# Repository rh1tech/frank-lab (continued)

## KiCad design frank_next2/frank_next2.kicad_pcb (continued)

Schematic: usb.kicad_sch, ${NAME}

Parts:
C1: 330 µF 6.3 V; CP_Elec_6.3x6.0
C3, C12, C14, C16, C17, C21, C22, C31, C73, C77, C86: 10 µF 25 V; C_0603_1608Metric_small_pads_Via_GND; LCSC C96446
C10, C19, C20, C69: 100 nF 50 V; C_0603_1608Metric_small_pads_Via_GND; LCSC C14663
C15: 100 µF 16 V; CP_Elec_6.3x6.0; LCSC C19270701
C26, C29: 12 pF 50 V; C_0603_1608Metric; LCSC C107034; not fitted
C30: 1 µF 50 V; C_0603_1608Metric_small_pads_Via_GND; LCSC C5199872
C76: 47 nF 50 V; C_0603_1608Metric_small_pads_Via; LCSC C1622
C85: 22 pF 50 V; C_0603_1608Metric_small_pads_Via; LCSC C1653
D1, D2: SMAJ5.0A; D_SMA; LCSC C83329
F2, F3: 2.6 A 6 V; Fuse_1812_4532Metric
J13, J14: USB4215-03-A; USB_C_Receptacle; LCSC C37616412
JP1: PWR Debug; SolderJumper-2_P1.3mm_Open_RoundedPad1.0x1.5mm
L3: 2.2 µH; L_Cenker_CKCS3015; LCSC C167747
L4: 330 Ω@100 MHz 2.5 A; L_0805_2012Metric; LCSC C76819
LD3: Green; LED_0603_1608Metric; LCSC C965804
R18, R47, R49, R52: 5.1 kΩ; R_0603_1608Metric; LCSC C23186
R19: 4.7 kΩ; R_0603_1608Metric; LCSC C23162; not fitted
R21: 39 kΩ; R_0603_1608Metric; LCSC C23153
R37: 300 kΩ; R_0603_1608Metric_small_pads_Via; LCSC C23024
R38: 1 MΩ; R_0603_1608Metric; LCSC C22935; not fitted
R39: 1 MΩ; R_0603_1608Metric_small_pads_Via; LCSC C22935
R42: 22 kΩ 1%; R_0603_1608Metric; LCSC C31850
R43: 100 kΩ 1%; R_0603_1608Metric_small_pads_Via; LCSC C25803
R45: 100 kΩ; R_0603_1608Metric; LCSC C25803
R53: 1 kΩ; R_0603_1608Metric_small_pads_Via; LCSC C21190
R57: 22 kΩ; R_0603_1608Metric; LCSC C31850
S5: SK12D07VG3NS; Switch_Slide_SK12D07VG3NS_PWR; Mouser Part Number 611-SK12D07VG3NS; LCSC C431547
TP2: VDD33; TestPoint_Pad_D1.0mm
TP5: VBUS; TestPoint_Pad_D1.0mm
TP6: VBUS_IN1; TestPoint_Pad_D1.0mm
TP7: VBUS_IN; TestPoint_Pad_D1.0mm
TP8: +5V_BUCK; TestPoint_Pad_D1.0mm
TP11: VBUS_IN2; TestPoint_Pad_D1.0mm
TP12: +3V3; TestPoint_Pad_D1.0mm
U5: TS3USB221RSER; UQFN-10; LCSC C130085
U6: SY8089AAAC; SOT-23-5; LCSC C78988
U8: TPS2116DRL; SOT-583-8; LCSC C3235557
U10, U11: TPD4S012DRYR; Mouser Part Number 595-TPD4S012DRYR; LCSC C96506
U16: CH334F; QFN-24-1EP_4x4mm_P0.5mm_EP2.7x2.7mm; LCSC C5187527
U17: CH217A; SOT-23-6; LCSC C54973763
U23: AO3401A; SOT-23-3L_AOS; LCSC C15127
Y1: 12 MHz; Crystal_SMD_3225-4Pin_3.2x2.5mm; LCSC C20625731

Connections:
+3V3: C10.1, C16.1, C17.1, C85.1, C86.1, L3.1, R43.1, R53.1, TP12.1 (1_1), U5.10 (VCC); also elsewhere on the board
/RP2350B/M_USB_DM: U5.7 (D-); also elsewhere on the board
/RP2350B/M_USB_DP: U5.8 (D+); also elsewhere on the board
/USB/+5V_BUCK: C12.1, C69.1, C77.1, L4.2, TP8.1 (1_1), U6.1 (EN), U6.4 (IN)
/USB/S_USB_DM: J13.5 (DN2), J13.7 (DN1), U10.2 (D-_); also elsewhere on the board
/USB/S_USB_DP: J13.6 (DP1), J13.8 (DP2), U10.1 (D+); also elsewhere on the board
/USB/US_D2+: J14.6 (DP1), J14.8 (DP2), U5.1 (1D+), U11.1 (D+)
/USB/US_D2-: J14.5 (DN2), J14.7 (DN1), U5.2 (1D-), U11.2 (D-_)
/USB/US_DH+: U5.3 (2D+), U16.15 (DPU+)
/USB/US_DH-: U5.4 (2D-), U16.14 (DMU-)
/USB/US_DS1+: U16.12 (DP1+); also elsewhere on the board
/USB/US_DS1-: U16.11 (DM1-); also elsewhere on the board
/USB/US_DS2+: U16.10 (DP2+); also elsewhere on the board
/USB/US_DS2-: U16.9 (DM2-); also elsewhere on the board
/USB/US_DS3+: U16.8 (DP3+); also elsewhere on the board
/USB/US_DS3-: U16.7 (DM3-); also elsewhere on the board
/USB/US_OVCUR: U16.1 (~OVCUR), U17.3 (FLAG#)
/USB/US_PWREN: U16.24 (~PWREN), U17.4 (EN#)
/USB/US_ST: R38.2, U8.8 (ST)
/USB/US_XTAL_N: C29.1, U16.3 (XO), Y1.3
/USB/US_XTAL_P: C26.1, U16.4 (XI), Y1.1
/USB/VBUS_A: C1.1, U17.1 (VOUT); also elsewhere on the board
/USB/VBUS_IN: C14.1, R39.1, TP7.1 (1_1), U8.2 (VOUT), U8.7 (VOUT), U23.2 (S)
/USB/VBUS_IN1: C19.1, C21.1, D1.1 (K), F2.2, R37.1, TP6.1 (1_1), U8.3 (VIN1), U8.5 (MODE)
/USB/VBUS_IN2: C20.1, C22.1, D2.1 (K), F3.2, TP11.1 (1_1), U8.6 (VIN2)
/USB/VBUS_J10: F3.1, J14.2 (VBUS), J14.11 (VBUS), U11.6 (VBUS)
/USB/VBUS_J11: F2.1, J13.2 (VBUS), J13.11 (VBUS), U10.6 (VBUS)
/USB/VDD33: C30.1, C31.1, TP2.1 (1_1), U16.20 (VDD33_{LDO})
/US_SEL: U5.9 (S); also elsewhere on the board
GND: C1.2, C3.2, C10.2, C12.2, C14.2, C15.2, C16.2, C17.2, C19.2, C20.2, C21.2, C22.2, C26.2, C29.2, C30.2, C31.2, C69.2, C73.2, C77.2, C86.2, D1.2 (A), D2.2 (A), J13.1 (GND), J13.12 (GND), J13.13 (SHIELD), J14.1 (GND), J14.12 (GND), J14.13 (SHIELD), JP1.1 (A), LD3.1 (K), R18.1, R19.2, R21.2, R42.2, R45.1, R47.1, R49.1, R52.1, S5.2, U5.5 (GND), U5.6 (~OE), U6.2 (GND), U8.1 (GND), U10.4 (GND), U11.4 (GND), U16.25 (GND), U17.2 (GND), Y1.2, Y1.4; also elsewhere on the board
unnamed: J13.4 (CC1), R49.2
unnamed: J13.10 (CC2), R18.2
unnamed: J14.4 (CC1), R47.2
unnamed: J14.10 (CC2), R52.2
unnamed: JP1.2 (B), R57.2, S5.3
unnamed: LD3.2 (A), R53.2
unnamed: C85.2, R42.1, R43.2, U6.5 (FB)
unnamed: L3.2, U6.3 (LX)
unnamed: R37.2, R38.1, R45.2, U8.4 (PR1)
unnamed: R19.1, U16.18 (PSELF)
unnamed: R21.1, U17.5 (ISET)
unnamed: C76.2, R39.2, R57.1, U23.1 (G)
VBUS: C3.1, C15.1, C73.1, C76.1, L4.1, TP5.1 (1_1), U16.19 (V5), U17.6 (VIN), U23.3 (D); also elsewhere on the board

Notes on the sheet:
F2 / F3: 2.6 A polyfuse, D1 / D2: SMAJ5.0A TVS per USB-C input (TPS2116 / CH217A / SY8089 are 6 V abs-max). U11 / U10 ESD at the connector.
Power path: J13 (VIN1) / J14 (VIN2) -> U8 TPS2116. J13 is preferred while its VBUS is above ~4 V (R37 / R45 on PR1, MODE tied to VIN1). R38: DNP. S5 -> U23 AO3401A P-FET: R39 holds it off, S5 pulls the gate low via R57, C76 = soft start. JP1 bypasses S5. VBUS -> L4 ferrite -> U6 SY8089 buck: 3V3 = 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
USB data: J13 -> RP2350A USB (direct). U5: RP2350B -> J14 (S = L, PC / BOOTSEL) or hub (S = H); S = USB_SEL from the latch. C29 / C26 DNP (CH334 has 16 pF inside). Needs a 5 V / 3 A supply.
5.1 kΩ CC pull-downs (Rd): both USB-C ports are sinks
USB-A VBUS: U17 CH217A gangs all 3 ports (CH334F gang mode), R21 39 kΩ = 1.54 A typ total. C1 330 µF polymer (Wurth 875105144010) on VBUS_A. C15 100 µF + C73 / C3 10 µF on VBUS.

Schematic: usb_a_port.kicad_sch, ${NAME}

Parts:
C25: 100 nF 50 V; C_0603_1608Metric; LCSC C14663
J3: AF 10.0 HC6.3; USB_A_Short; LCSC C456017
U15: TPD4S012DRYR; Mouser Part Number 595-TPD4S012DRYR; LCSC C96506

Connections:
/USB/US_DS1+: J3.3 (D+), U15.1 (D+); also elsewhere on the board
/USB/US_DS1-: J3.2 (D-), U15.2 (D-_); also elsewhere on the board
/USB/VBUS_A: C25.1, J3.1 (VBUS), U15.6 (VBUS); also elsewhere on the board
GND: C25.2, J3.4 (GND), J3.5 (Shield), U15.4 (GND); also elsewhere on the board

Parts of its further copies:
C23, C24: 100 nF 50 V; C_0603_1608Metric; LCSC C14663
J1, J2: AF 10.0 HC6.3; USB_A_Short; LCSC C456017
U13, U14: TPD4S012DRYR; Mouser Part Number 595-TPD4S012DRYR; LCSC C96506

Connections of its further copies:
/USB/US_DS2+: J2.3 (D+), U14.1 (D+); also elsewhere on the board
/USB/US_DS2-: J2.2 (D-), U14.2 (D-_); also elsewhere on the board
/USB/US_DS3+: J1.3 (D+), U13.1 (D+); also elsewhere on the board
/USB/US_DS3-: J1.2 (D-), U13.2 (D-_); also elsewhere on the board
/USB/VBUS_A: C23.1, C24.1, J1.1 (VBUS), J2.1 (VBUS), U13.6 (VBUS), U14.6 (VBUS); also elsewhere on the board
GND: C23.2, C24.2, J1.4 (GND), J1.5 (Shield), J2.4 (GND), J2.5 (Shield), U13.4 (GND), U14.4 (GND); also elsewhere on the board

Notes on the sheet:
VBUS_A: switched USB-A VBUS from the shared CH217A (USB sheet). C25 / C23 / C24 100 nF at the connector; TPD4S012: ESD for D+ / D- / VBUS.

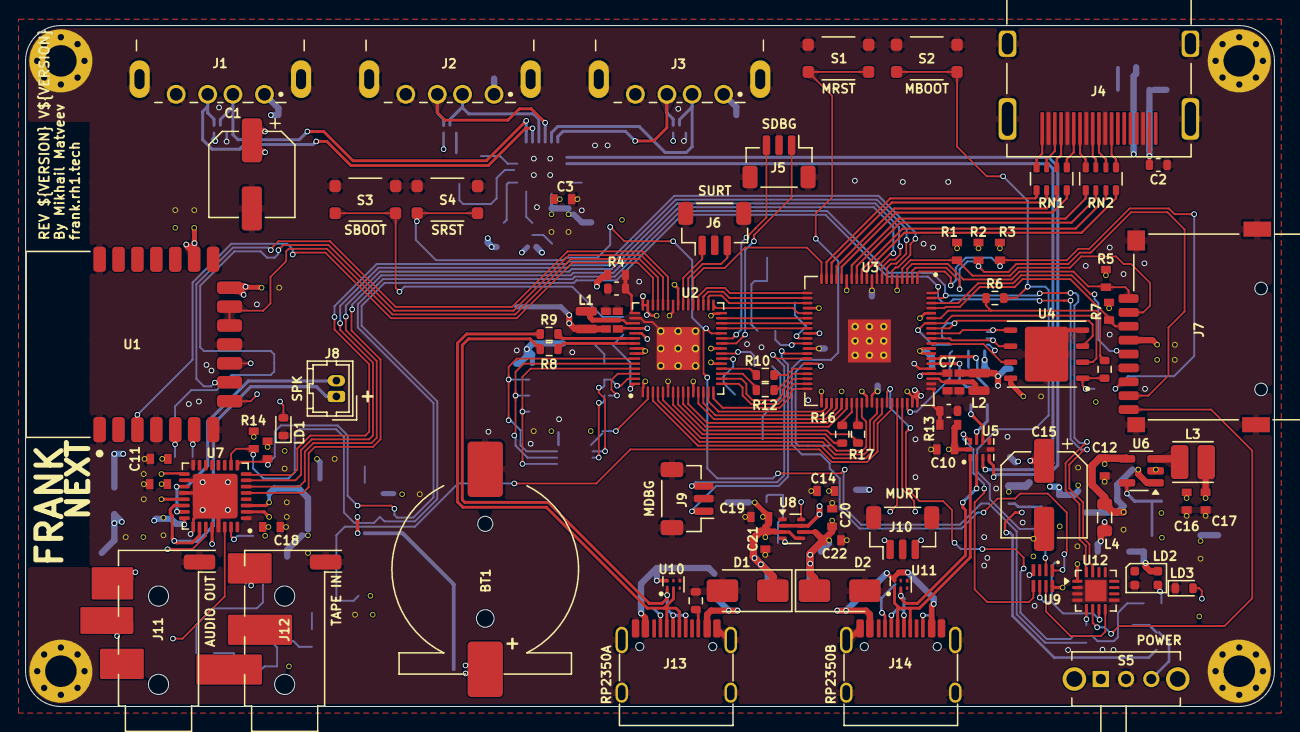
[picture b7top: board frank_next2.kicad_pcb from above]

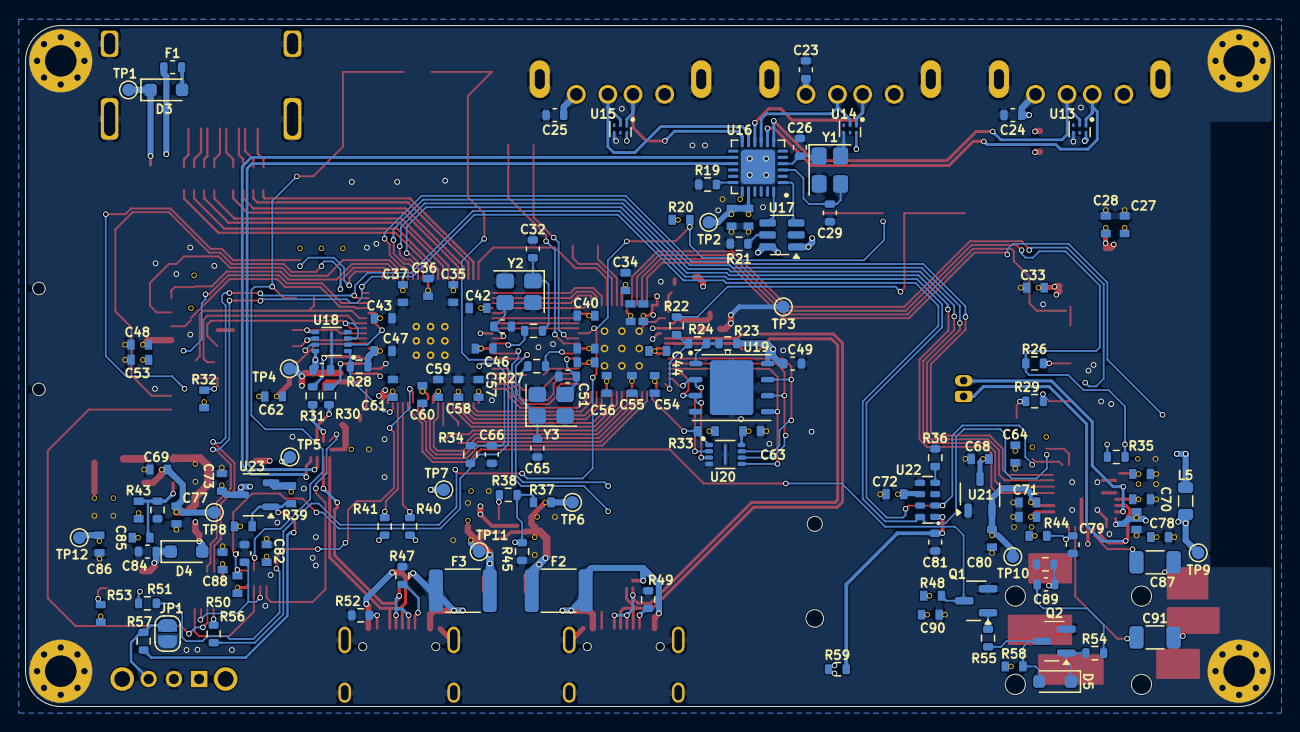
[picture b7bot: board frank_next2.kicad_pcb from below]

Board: 4 copper layers, 99.0 x 54.0 mm, 233 parts (146 on the bottom side), 180 nets.

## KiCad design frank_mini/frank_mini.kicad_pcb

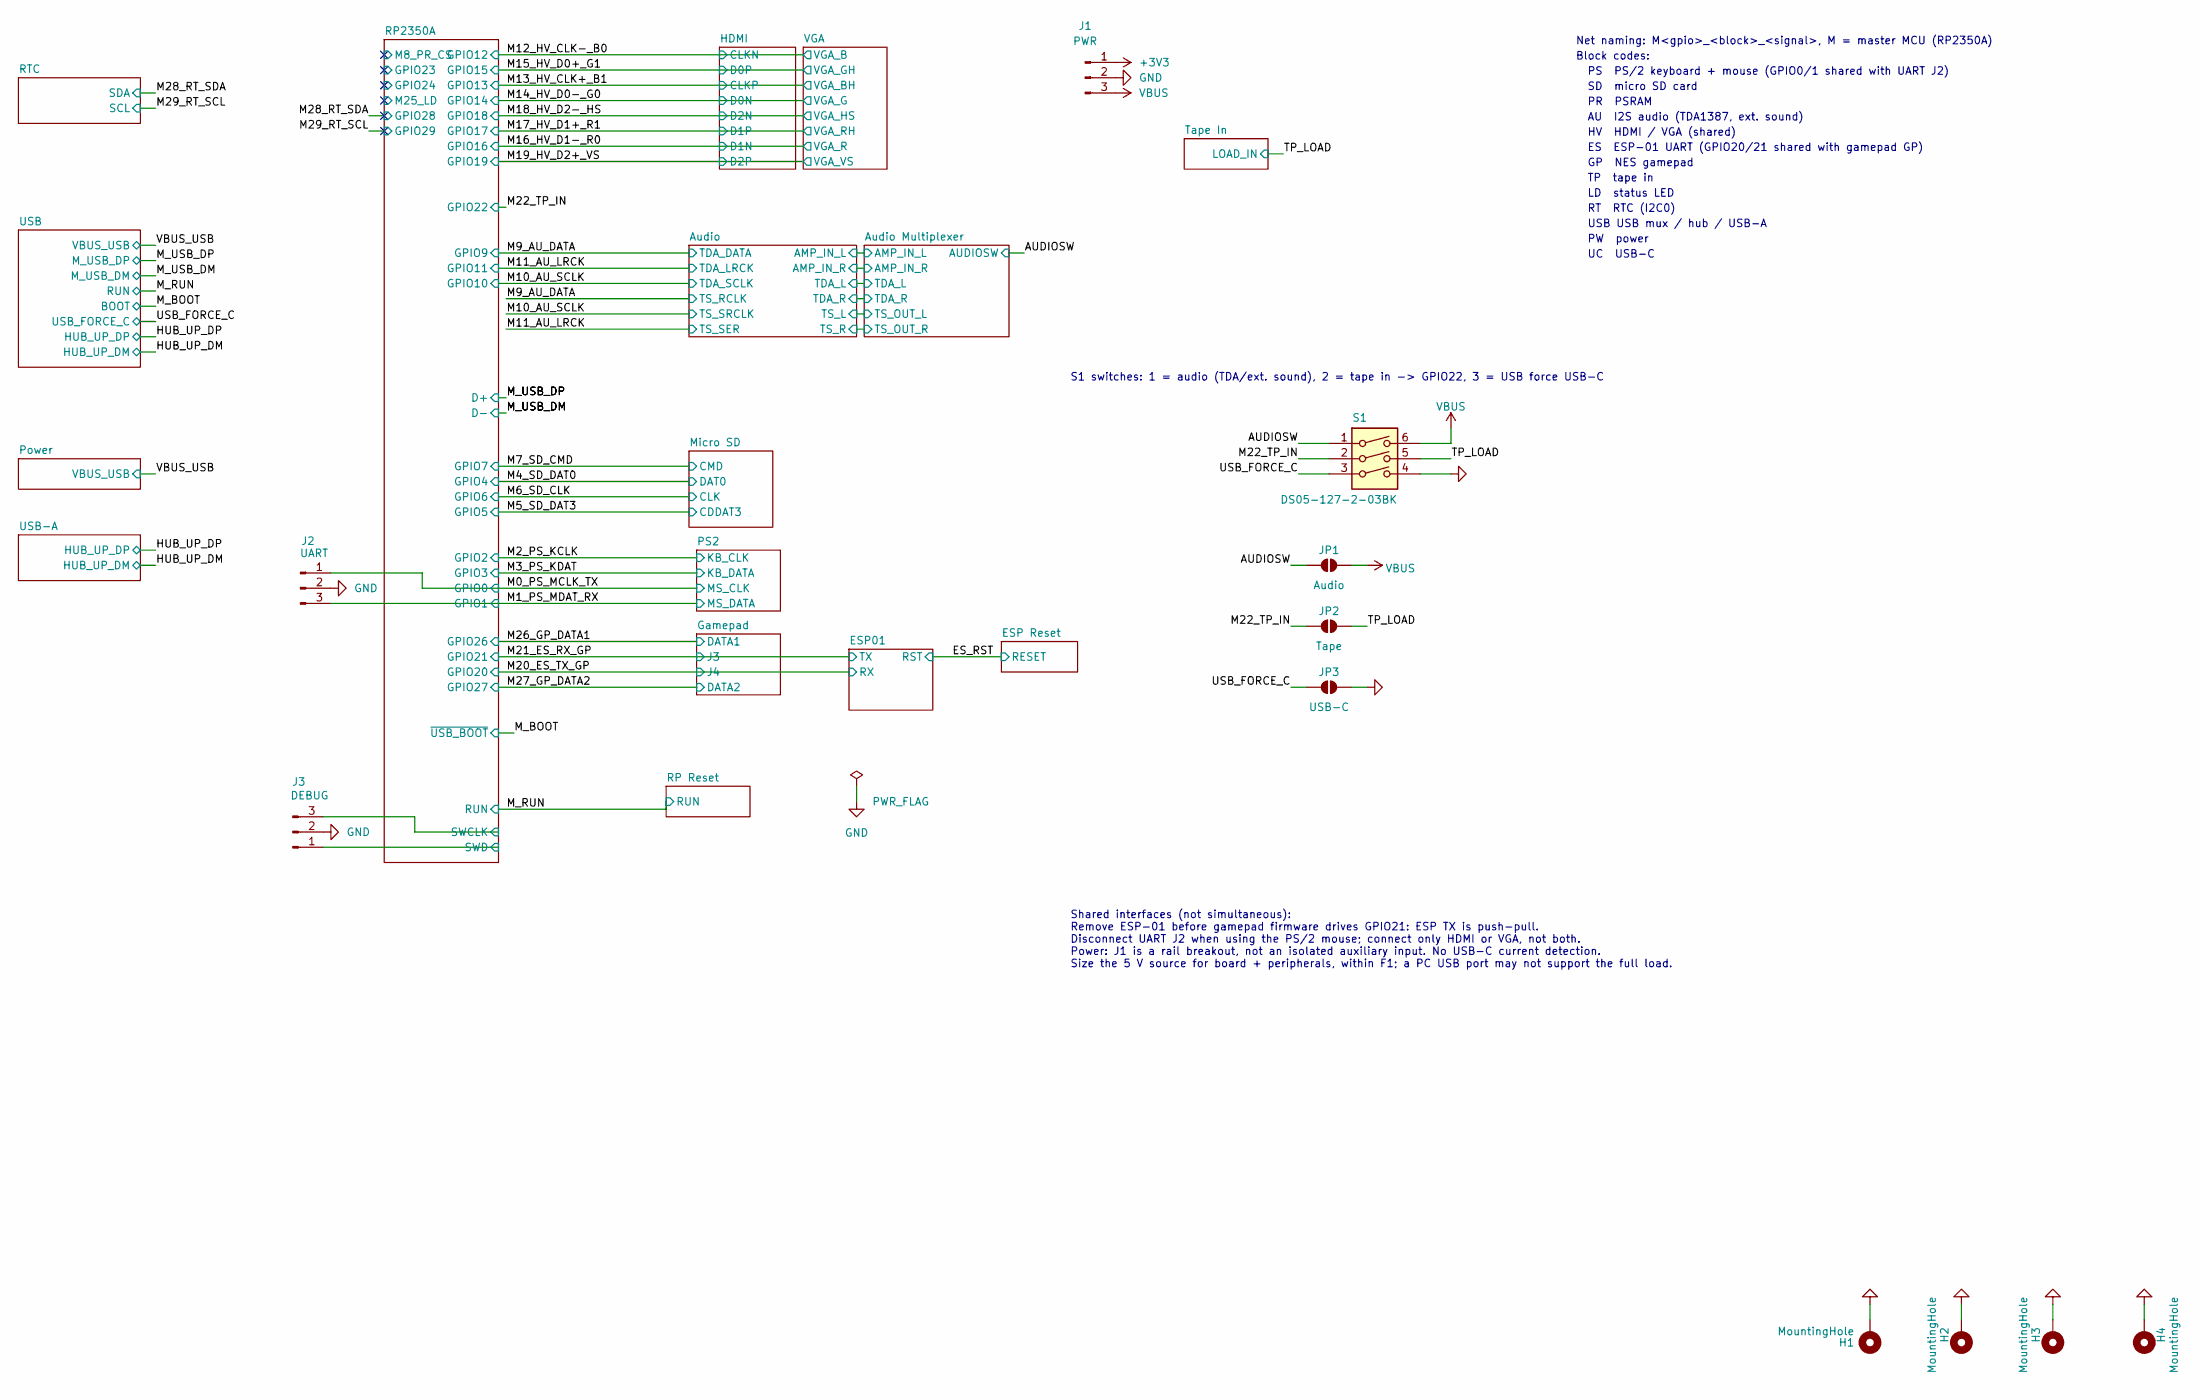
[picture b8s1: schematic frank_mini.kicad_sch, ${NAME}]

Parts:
H1, H2, H3, H4: MountingHole; MountingHole_2.5mm_Pad_Via
J1: PWR; PinHeader_1x03_P2.54mm
J2: UART; JST_SH_BM03B-SRSS-TB_1x03-1MP_P1.00mm_Vertical
J3: DEBUG; JST_SH_BM03B-SRSS-TB_1x03-1MP_P1.00mm_Vertical
JP1: Audio; SolderJumper-2_P1.3mm_Open_RoundedPad1.0x1.5mm
JP2: Tape; SolderJumper-2_P1.3mm_Open_RoundedPad1.0x1.5mm
JP3: USB-C; SolderJumper-2_P1.3mm_Open_RoundedPad1.0x1.5mm
S1: DS05-127-2-03BK; SW_DS05-127-2-03BK-SMT-TR

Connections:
+3V3: J1.1; also elsewhere on the board
/AUDIOSW: JP1.1 (A), S1.1; also elsewhere on the board
/M0_PS_MCLK_TX: J2.1; also elsewhere on the board
/M1_PS_MDAT_RX: J2.3; also elsewhere on the board
/M22_TP_IN: JP2.1 (A), S1.2; also elsewhere on the board
/RP2350A/SWCLK: J3.3; also elsewhere on the board
/RP2350A/SWD: J3.1; also elsewhere on the board
/TP_LOAD: JP2.2 (B), S1.5; also elsewhere on the board
/USB_FORCE_C: JP3.1 (A), S1.3; also elsewhere on the board
GND: H1.1 (1_1), H2.1 (1_1), H3.1 (1_1), H4.1 (1_1), J1.2, J2.2, J3.2, JP3.2 (B), S1.4; also elsewhere on the board
VBUS: J1.3, JP1.2 (B), S1.6; also elsewhere on the board

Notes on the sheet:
UC USB-C
AU I2S audio (TDA1387, ext. sound)
S1 switches: 1 = audio (TDA/ext. sound), 2 = tape in -> GPIO22, 3 = USB force USB-C
TP tape in
PS PS/2 keyboard + mouse (GPIO0/1 shared with UART J2)
SD micro SD card
USB USB mux / hub / USB-A
PW power
GP NES gamepad
RT RTC (I2C0)
Block codes:
LD status LED
PR PSRAM
Net naming: M<gpio>_<block>_<signal>, M = master MCU (RP2350A)
HV HDMI / VGA (shared)
ES ESP-01 UART (GPIO20/21 shared with gamepad GP)
Shared interfaces (not simultaneous): Remove ESP-01 before gamepad firmware drives GPIO21: ESP TX is push-pull. Disconnect UART J2 when using the PS/2 mouse; connect only HDMI or VGA, not both. Power: J1 is a rail breakout, not an isolated auxiliary input. No USB-C current detection. Size the 5 V s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

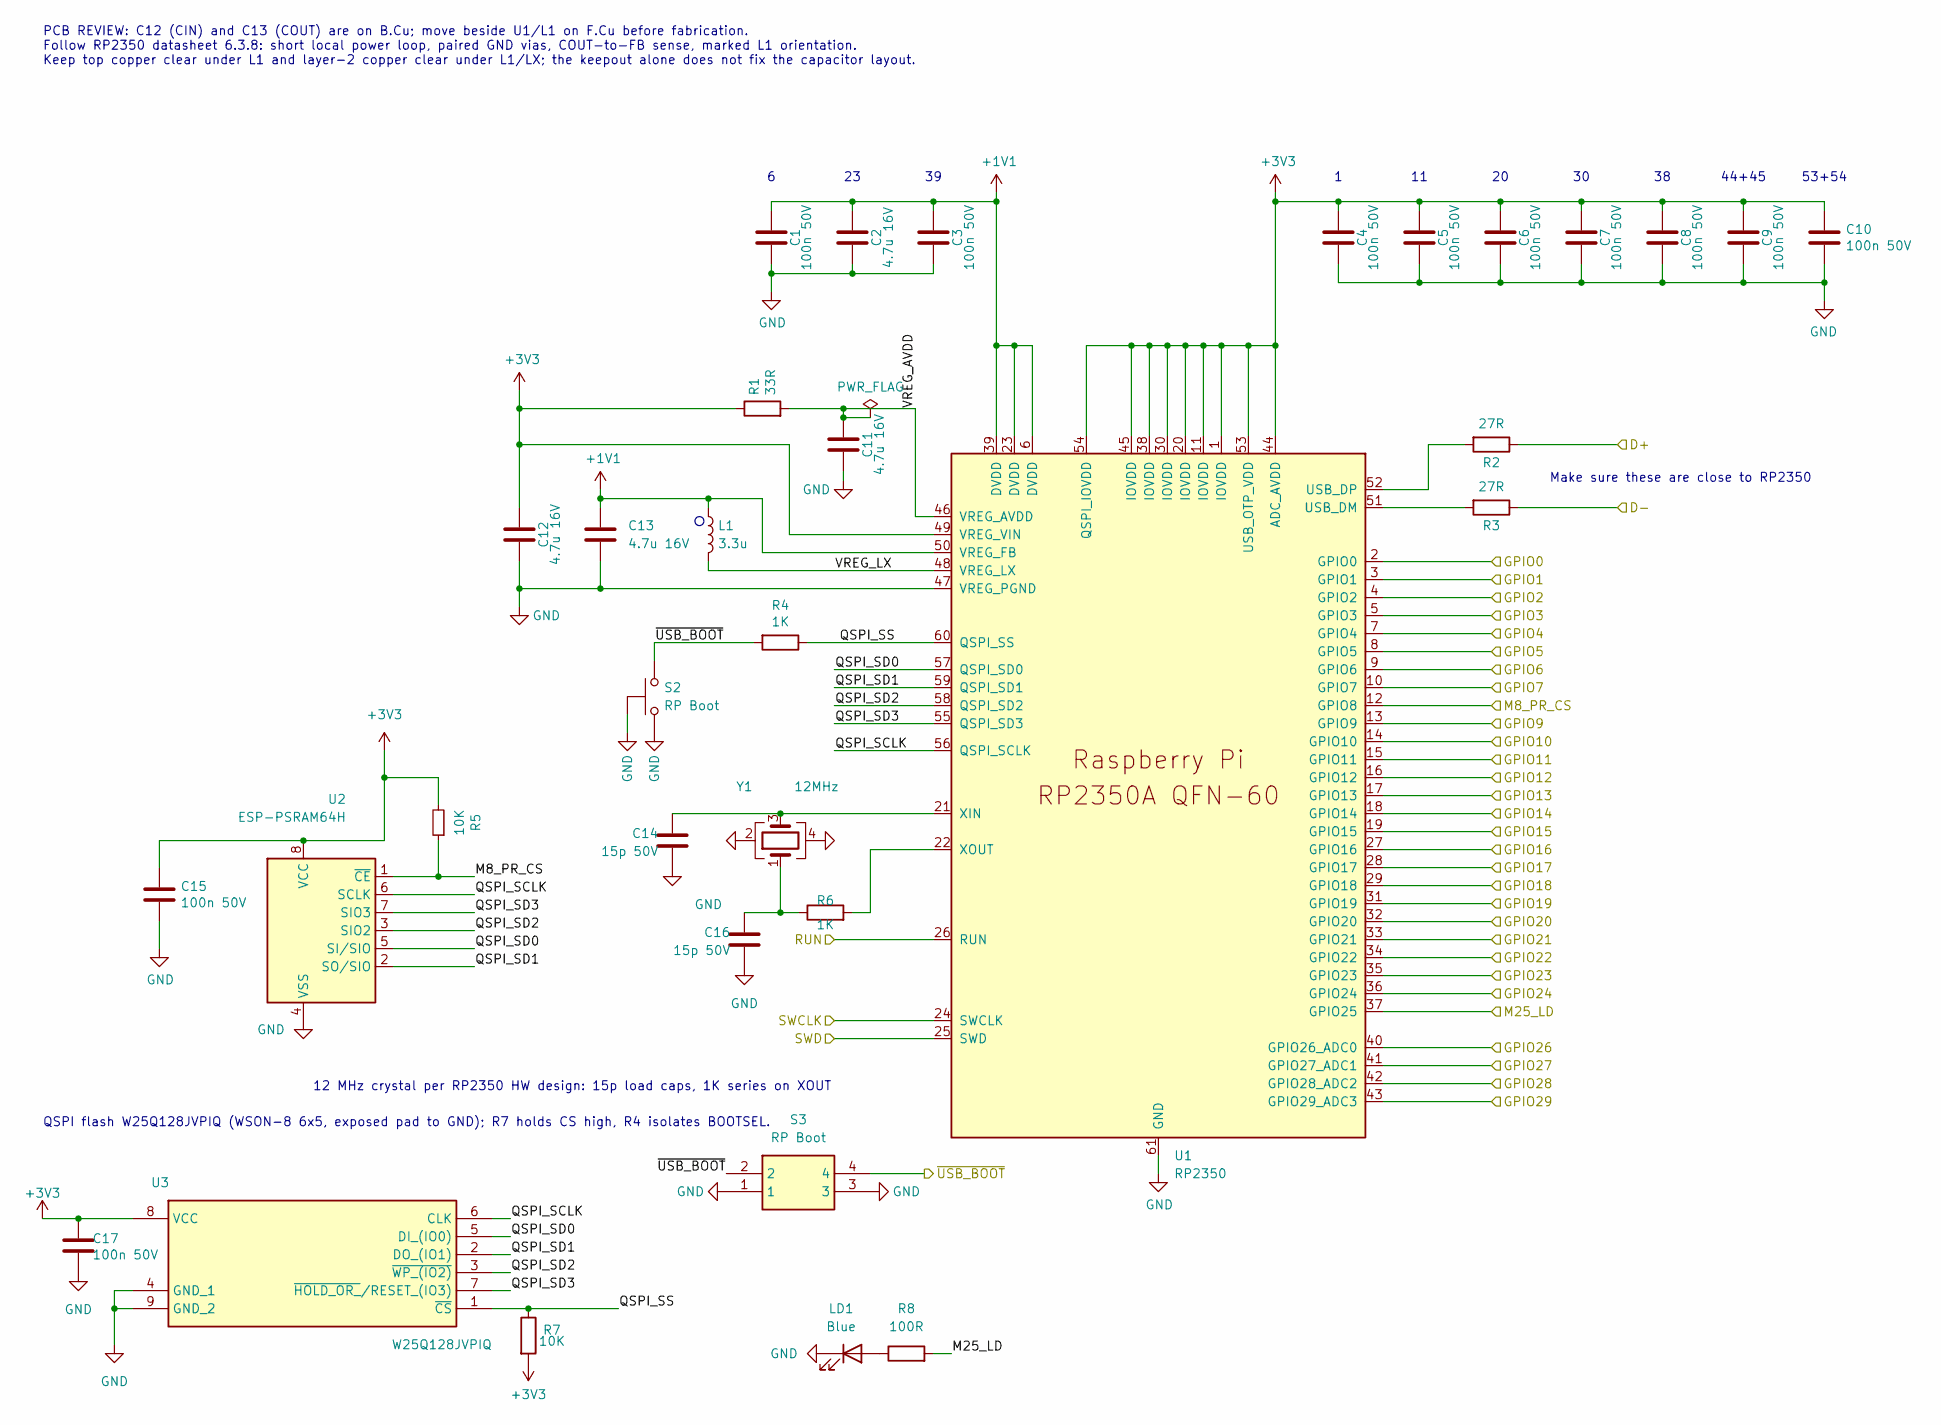
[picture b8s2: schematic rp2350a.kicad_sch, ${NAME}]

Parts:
C1, C3, C4, C5, C6, C7, C8, C9, C10, C15, C17: 100n 50V; C_0603_1608Metric
C2, C11, C12, C13: 4.7u 16V; C_0603_1608Metric
C14, C16: 15p 50V; C_0603_1608Metric
L1: 3.3u; L_pol_2016
LD1: Blue; LED_0603_1608Metric
R1: 33R; R_0603_1608Metric
R2, R3: 27R; R_0603_1608Metric
R4, R6: 1K; R_0603_1608Metric
R5, R7: 10K; R_0603_1608Metric
R8: 100R; R_0603_1608Metric
S2: RP Boot; TS-1234VW
S3: RP Boot; KMR_2; Mouser Part Number 611-KMR221G-LFS
U1: RP2350; QFN-60_RP2350A
U2: ESP-PSRAM64H; SO-8
U3: W25Q128JVPIQ; WSON-8-1EP_6x5mm_P1.27mm_EP3.45x4.35mm
Y1: 12MHz; Crystal_SMD_3225-4Pin_3.2x2.5mm

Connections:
+1V1: C1.1, C2.1, C3.1, C13.1, L1.1, U1.6 (DVDD), U1.23 (DVDD), U1.39 (DVDD), U1.50 (VREG_FB); also elsewhere on the board
+3V3: C4.1, C5.1, C6.1, C7.1, C8.1, C9.1, C10.1, C12.1, C15.1, C17.1, R1.1, R5.2, R7.2, U1.1 (IOVDD), U1.11 (IOVDD), U1.20 (IOVDD), U1.30 (IOVDD), U1.38 (IOVDD), U1.44 (ADC_AVDD), U1.45 (IOVDD), U1.49 (VREG_VIN), U1.53 (USB_OTP_VDD), U1.54 (QSPI_IOVDD), U2.8 (VCC), U3.8 (VCC); also elsewhere on the board
/M0_PS_MCLK_TX: U1.2 (GPIO0); also elsewhere on the board
/M1_PS_MDAT_RX: U1.3 (GPIO1); also elsewhere on the board
/M2_PS_KCLK: U1.4 (GPIO2); also elsewhere on the board
/M3_PS_KDAT: U1.5 (GPIO3); also elsewhere on the board
/M4_SD_DAT0: U1.7 (GPIO4); also elsewhere on the board
/M5_SD_DAT3: U1.8 (GPIO5); also elsewhere on the board
/M6_SD_CLK: U1.9 (GPIO6); also elsewhere on the board
/M7_SD_CMD: U1.10 (GPIO7); also elsewhere on the board
/M9_AU_DATA: U1.13 (GPIO9); also elsewhere on the board
/M10_AU_SCLK: U1.14 (GPIO10); also elsewhere on the board
/M11_AU_LRCK: U1.15 (GPIO11); also elsewhere on the board
/M12_HV_CLK-_B0: U1.16 (GPIO12); also elsewhere on the board
/M13_HV_CLK+_B1: U1.17 (GPIO13); also elsewhere on the board
/M14_HV_D0-_G0: U1.18 (GPIO14); also elsewhere on the board
/M15_HV_D0+_G1: U1.19 (GPIO15); also elsewhere on the board
/M16_HV_D1-_R0: U1.27 (GPIO16); also elsewhere on the board
/M17_HV_D1+_R1: U1.28 (GPIO17); also elsewhere on the board
/M18_HV_D2-_HS: U1.29 (GPIO18); also elsewhere on the board
/M19_HV_D2+_VS: U1.31 (GPIO19); also elsewhere on the board
/M20_ES_TX_GP: U1.32 (GPIO20); also elsewhere on the board
/M21_ES_RX_GP: U1.33 (GPIO21); also elsewhere on the board
/M22_TP_IN: U1.34 (GPIO22); also elsewhere on the board
/M26_GP_DATA1: U1.40 (GPIO26_ADC0); also elsewhere on the board
/M27_GP_DATA2: U1.41 (GPIO27_ADC1); also elsewhere on the board
/M28_RT_SDA: U1.42 (GPIO28_ADC2); also elsewhere on the board
/M29_RT_SCL: U1.43 (GPIO29_ADC3); also elsewhere on the board
/M_BOOT: R4.2, S2.2, S3.2, S3.4; also elsewhere on the board
/M_RUN: U1.26 (RUN); also elsewhere on the board
/M_USB_DM: R3.1; also elsewhere on the board
/M_USB_DP: R2.1; also elsewhere on the board
/RP2350A/GPIO23: U1.35 (GPIO23)
/RP2350A/GPIO24: U1.36 (GPIO24)
/RP2350A/M8_PR_CS: R5.1, U1.12 (GPIO8), U2.1 (~CE)
/RP2350A/M25_LD: R8.2, U1.37 (GPIO25)
/RP2350A/QSPI_SCLK: U1.56 (QSPI_SCLK), U2.6 (SCLK), U3.6 (CLK)
/RP2350A/QSPI_SD0: U1.57 (QSPI_SD0), U2.5 (SI/SIO), U3.5 (DI_(IO0))
/RP2350A/QSPI_SD1: U1.59 (QSPI_SD1), U2.2 (SO/SIO), U3.2 (DO_(IO1))
/RP2350A/QSPI_SD2: U1.58 (QSPI_SD2), U2.3 (SIO2), U3.3 (~WP_(IO2))
/RP2350A/QSPI_SD3: U1.55 (QSPI_SD3), U2.7 (SIO3), U3.7 (~HOLD_OR_/RESET_(IO3))
/RP2350A/QSPI_SS: R4.1, R7.1, U1.60 (QSPI_SS), U3.1 (~CS)
/RP2350A/SWCLK: U1.24 (SWCLK); also elsewhere on the board
/RP2350A/SWD: U1.25 (SWD); also elsewhere on the board
/RP2350A/VREG_AVDD: C11.1, R1.2, U1.46 (VREG_AVDD)
/RP2350A/VREG_LX: L1.2, U1.48 (VREG_LX)
GND: C1.2, C2.2, C3.2, C4.2, C5.2, C6.2, C7.2, C8.2, C9.2, C10.2, C11.2, C12.2, C13.2, C14.2, C15.2, C16.2, C17.2, LD1.1 (K), S2.1, S2.3 (GND), S3.1, S3.3, U1.47 (VREG_PGND), U1.61 (GND), U2.4 (VSS), U3.4 (GND_1), U3.9 (GND_2), Y1.2, Y1.4; also elsewhere on the board
unnamed: C16.1, R6.1, Y1.1
unnamed: LD1.2 (A), R8.1
unnamed: R3.2, U1.51 (USB_DM)
unnamed: R2.2, U1.52 (USB_DP)
unnamed: C14.1, U1.21 (XIN), Y1.3
unnamed: R6.2, U1.22 (XOUT)

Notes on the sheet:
12 MHz crystal per RP2350 HW design: 15p load caps, 1K series on XOUT
53+54
44+45
Make sure these are close to RP2350
QSPI flash W25Q128JVPIQ (WSON-8 6x5, exposed pad to GND); R7 holds CS high, R4 isolates BOOTSEL.
PCB REVIEW: C12 (CIN) and C13 (COUT) are on B.Cu; move beside U1/L1 on F.Cu before fabrication. Follow RP2350 datasheet 6.3.8: short local power loop, paired GND vias, COUT-to-FB sense, marked L1 orientation. Keep top copper clear under L1 and layer-2 copper clear under L1/LX; the keepout alone doe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

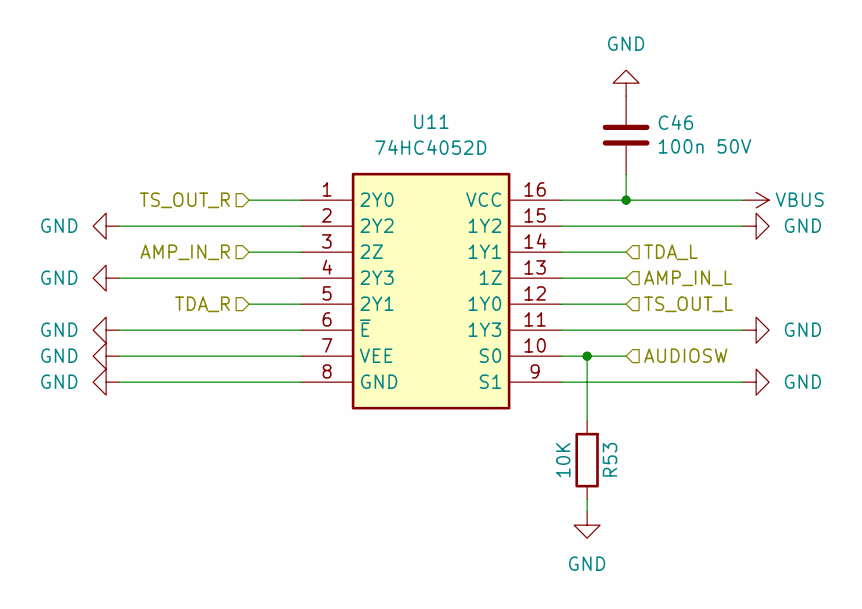
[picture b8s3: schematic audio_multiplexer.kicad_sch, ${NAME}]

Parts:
C46: 100n 50V; C_0603_1608Metric
R53: 10K; R_0603_1608Metric
U11: 74HC4052D; SOP-16_P1.27mm; Mouser Part Number 771-74HC4052D-T

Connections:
/AUDIOSW: R53.2, U11.10 (S0); also elsewhere on the board
/Audio Multiplexer/AMP_IN_L: U11.13 (1Z); also elsewhere on the board
/Audio Multiplexer/AMP_IN_R: U11.3 (2Z); also elsewhere on the board
/Audio Multiplexer/TDA_L: U11.14 (1Y1); also elsewhere on the board
/Audio Multiplexer/TDA_R: U11.5 (2Y1); also elsewhere on the board
/Audio Multiplexer/TS_OUT_L: U11.12 (1Y0); also elsewhere on the board
/Audio Multiplexer/TS_OUT_R: U11.1 (2Y0); also elsewhere on the board
GND: C46.1, R53.1, U11.2 (2Y2), U11.4 (2Y3), U11.6 (~E), U11.7 (VEE), U11.8 (GND), U11.9 (S1), U11.11 (1Y3), U11.15 (1Y2); also elsewhere on the board
VBUS: C46.2, U11.16 (VCC); also elsewhere on the board

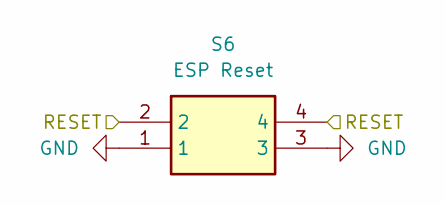
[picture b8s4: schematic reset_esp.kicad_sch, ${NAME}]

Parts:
S6: ESP Reset; KMR_2; Mouser Part Number 611-KMR221G-LFS

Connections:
/ES_RST: S6.2, S6.4; also elsewhere on the board
GND: S6.1, S6.3; also elsewhere on the board

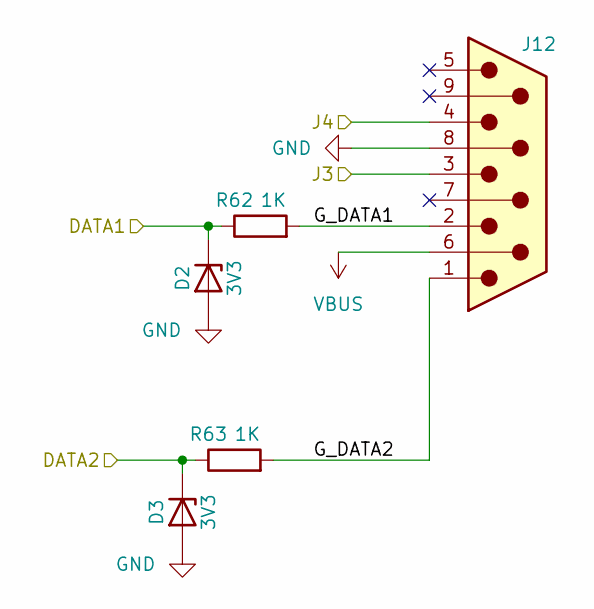
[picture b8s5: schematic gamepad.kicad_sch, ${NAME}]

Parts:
D2, D3: 3V3; D_SOD-323
J12: GP2; DSUB-9_Male_TopMount
R62, R63: 1K; R_0603_1608Metric

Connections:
/Gamepad/G_DATA1: J12.2, R62.2
/Gamepad/G_DATA2: J12.1, R63.2
/M20_ES_TX_GP: J12.4; also elsewhere on the board
/M21_ES_RX_GP: J12.3; also elsewhere on the board
/M26_GP_DATA1: D2.1 (K), R62.1; also elsewhere on the board
/M27_GP_DATA2: D3.1 (K), R63.1; also elsewhere on the board
GND: D2.2 (A), D3.2 (A), J12.8; also elsewhere on the board
VBUS: J12.6; also elsewhere on the board

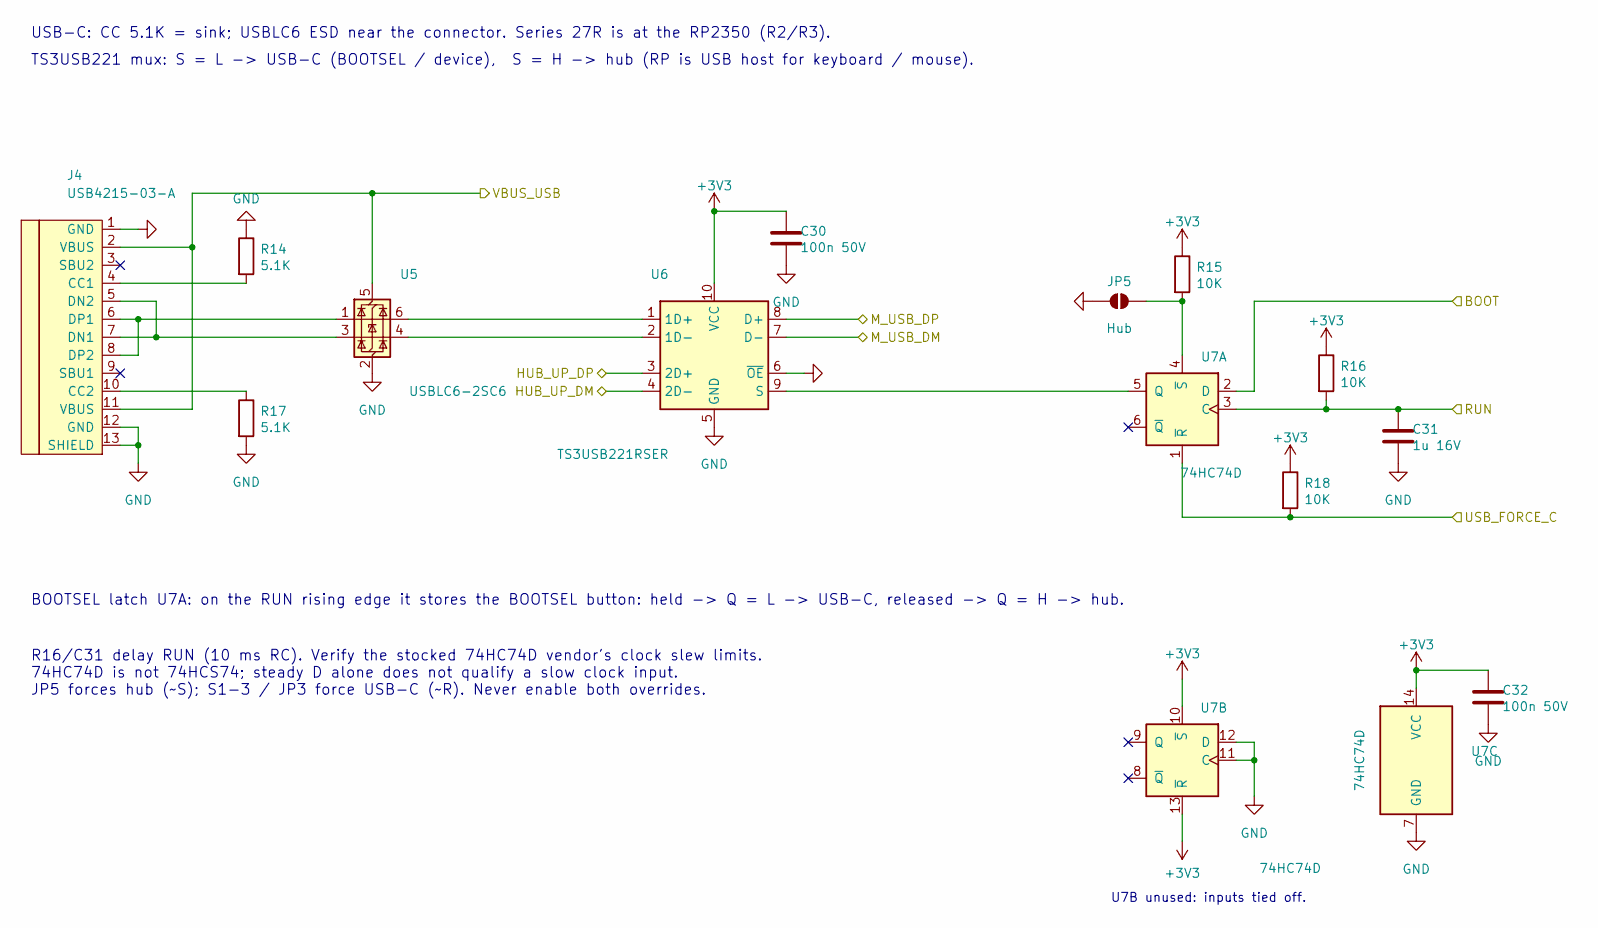
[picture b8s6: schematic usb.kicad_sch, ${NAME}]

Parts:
C30, C32: 100n 50V; C_0603_1608Metric
C31: 1u 16V; C_0603_1608Metric
J4: USB4215-03-A; USB_C_Receptacle; LCSC C165948
JP5: Hub; SolderJumper-2_P1.3mm_Open_RoundedPad1.0x1.5mm
R14, R17: 5.1K; R_0603_1608Metric
R15, R16, R18: 10K; R_0603_1608Metric
U5: USBLC6-2SC6; SOT-23-6
U6: TS3USB221RSER; UQFN-10
U7: 74HC74D; SOIC-14_P1.27mm

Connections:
+3V3: C30.1, C32.1, R15.1, R16.1, R18.1, U6.10 (VCC), U7.10 (~S), U7.13 (~R), U7.14 (VCC); also elsewhere on the board
/HUB_UP_DM: U6.4 (2D-); also elsewhere on the board
/HUB_UP_DP: U6.3 (2D+); also elsewhere on the board
/M_BOOT: U7.2 (D); also elsewhere on the board
/M_RUN: C31.1, R16.2, U7.3 (C); also elsewhere on the board
/M_USB_DM: U6.7 (D-); also elsewhere on the board
/M_USB_DP: U6.8 (D+); also elsewhere on the board
/USB_FORCE_C: R18.2, U7.1 (~R); also elsewhere on the board
/VBUS_USB: J4.2 (VBUS), J4.11 (VBUS), U5.5 (VBUS); also elsewhere on the board
GND: C30.2, C31.2, C32.2, J4.1 (GND), J4.12 (GND), J4.13 (SHIELD), JP5.1 (A), R14.1, R17.2, U5.2 (GND), U6.5 (GND), U6.6 (~OE), U7.7 (GND), U7.11 (C), U7.12 (D); also elsewhere on the board
unnamed: J4.4 (CC1), R14.2
unnamed: J4.10 (CC2), R17.1
unnamed: J4.5 (DN2), J4.7 (DN1), U5.3 (I/O2)
unnamed: J4.6 (DP1), J4.8 (DP2), U5.1 (I/O1)
unnamed: JP5.2 (B), R15.2, U7.4 (~S)
unnamed: U5.6 (I/O1), U6.1 (1D+)
unnamed: U5.4 (I/O2), U6.2 (1D-)
unnamed: U6.9 (S), U7.5 (Q)

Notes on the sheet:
U7B unused: inputs tied off.
USB-C: CC 5.1K = sink; USBLC6 ESD near the connector. Series 27R is at the RP2350 (R2/R3).
BOOTSEL latch U7A: on the RUN rising edge it stores the BOOTSEL button: held -> Q = L -> USB-C, released -> Q = H -> hub.
R16/C31 delay RUN (10 ms RC). Verify the stocked 74HC74D vendor's clock slew limits. 74HC74D is not 74HCS74; steady D alone does not qualify a slow clock input. JP5 forces hub (~S); S1-3 / JP3 force USB-C (~R). Never enable both overrides.
TS3USB221 mux: S = L -> USB-C (BOOTSEL / device), S = H -> hub (RP is USB host for keyboard / mouse).

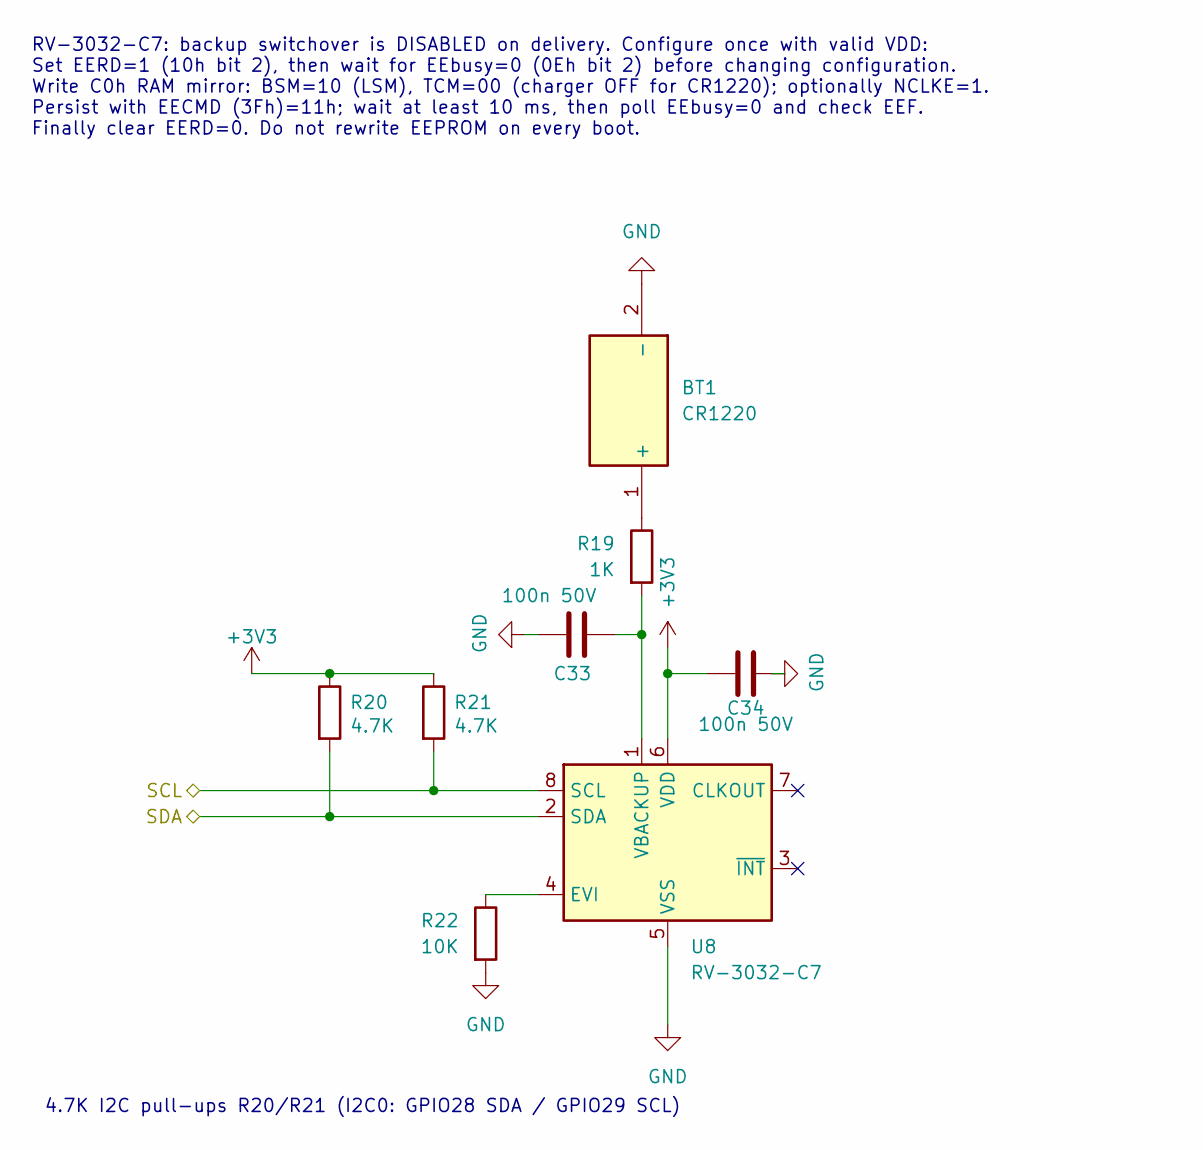
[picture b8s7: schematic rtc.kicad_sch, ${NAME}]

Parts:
BT1: CR1220; Battery_CR1220_MYOUNG_BS-12-B3AA003; Manufacturer_Part_Number BS-12-B3AA003; LCSC C964723
C33, C34: 100n 50V; C_0603_1608Metric; LCSC C14663
R19: 1K; R_0603_1608Metric; LCSC C21190
R20, R21: 4.7K; R_0603_1608Metric
R22: 10K; R_0603_1608Metric; LCSC C2906982
U8: RV-3032-C7; LCSC C5127802

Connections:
+3V3: C34.1, R20.1, R21.1, U8.6 (VDD); also elsewhere on the board
/M28_RT_SDA: R20.2, U8.2 (SDA); also elsewhere on the board
/M29_RT_SCL: R21.2, U8.8 (SCL); also elsewhere on the board
GND: BT1.2 (-), C33.1, C34.2, R22.2, U8.5 (VSS); also elsewhere on the board
unnamed: BT1.1 (+), R19.1
unnamed: R22.1, U8.4 (EVI)
unnamed: C33.2, R19.2, U8.1 (VBACKUP)

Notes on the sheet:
RV-3032-C7: backup switchover is DISABLED on delivery. Configure once with valid VDD: Set EERD=1 (10h bit 2), then wait for EEbusy=0 (0Eh bit 2) before changing configuration. Write C0h RAM mirror: BSM=10 (LSM), TCM=00 (charger OFF for CR1220); optionally NCLKE=1. Persist with EECMD (3Fh)=11h; wait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
4.7K I2C pull-ups R20/R21 (I2C0: GPIO28 SDA / GPIO29 SCL)
